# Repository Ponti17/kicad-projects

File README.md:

# KiCad Projects

## Torpedo-III

A clone of ECP audios Torpedo-III amplifier with a few changes:
- Off board PS
- On board output CCS
- Cascade tube CCS
- Constant current heater

## T-GND

A PCB for combining high and low current grounds correctly.

A clone of the PCB from the Wolverine diyAudio thread. Original done by stuartmp

## GND-LIFT

A PCB for lifting circuit ground from chassis ground.

Also a clone of a PCB from the Wolverine diyAudio thread.

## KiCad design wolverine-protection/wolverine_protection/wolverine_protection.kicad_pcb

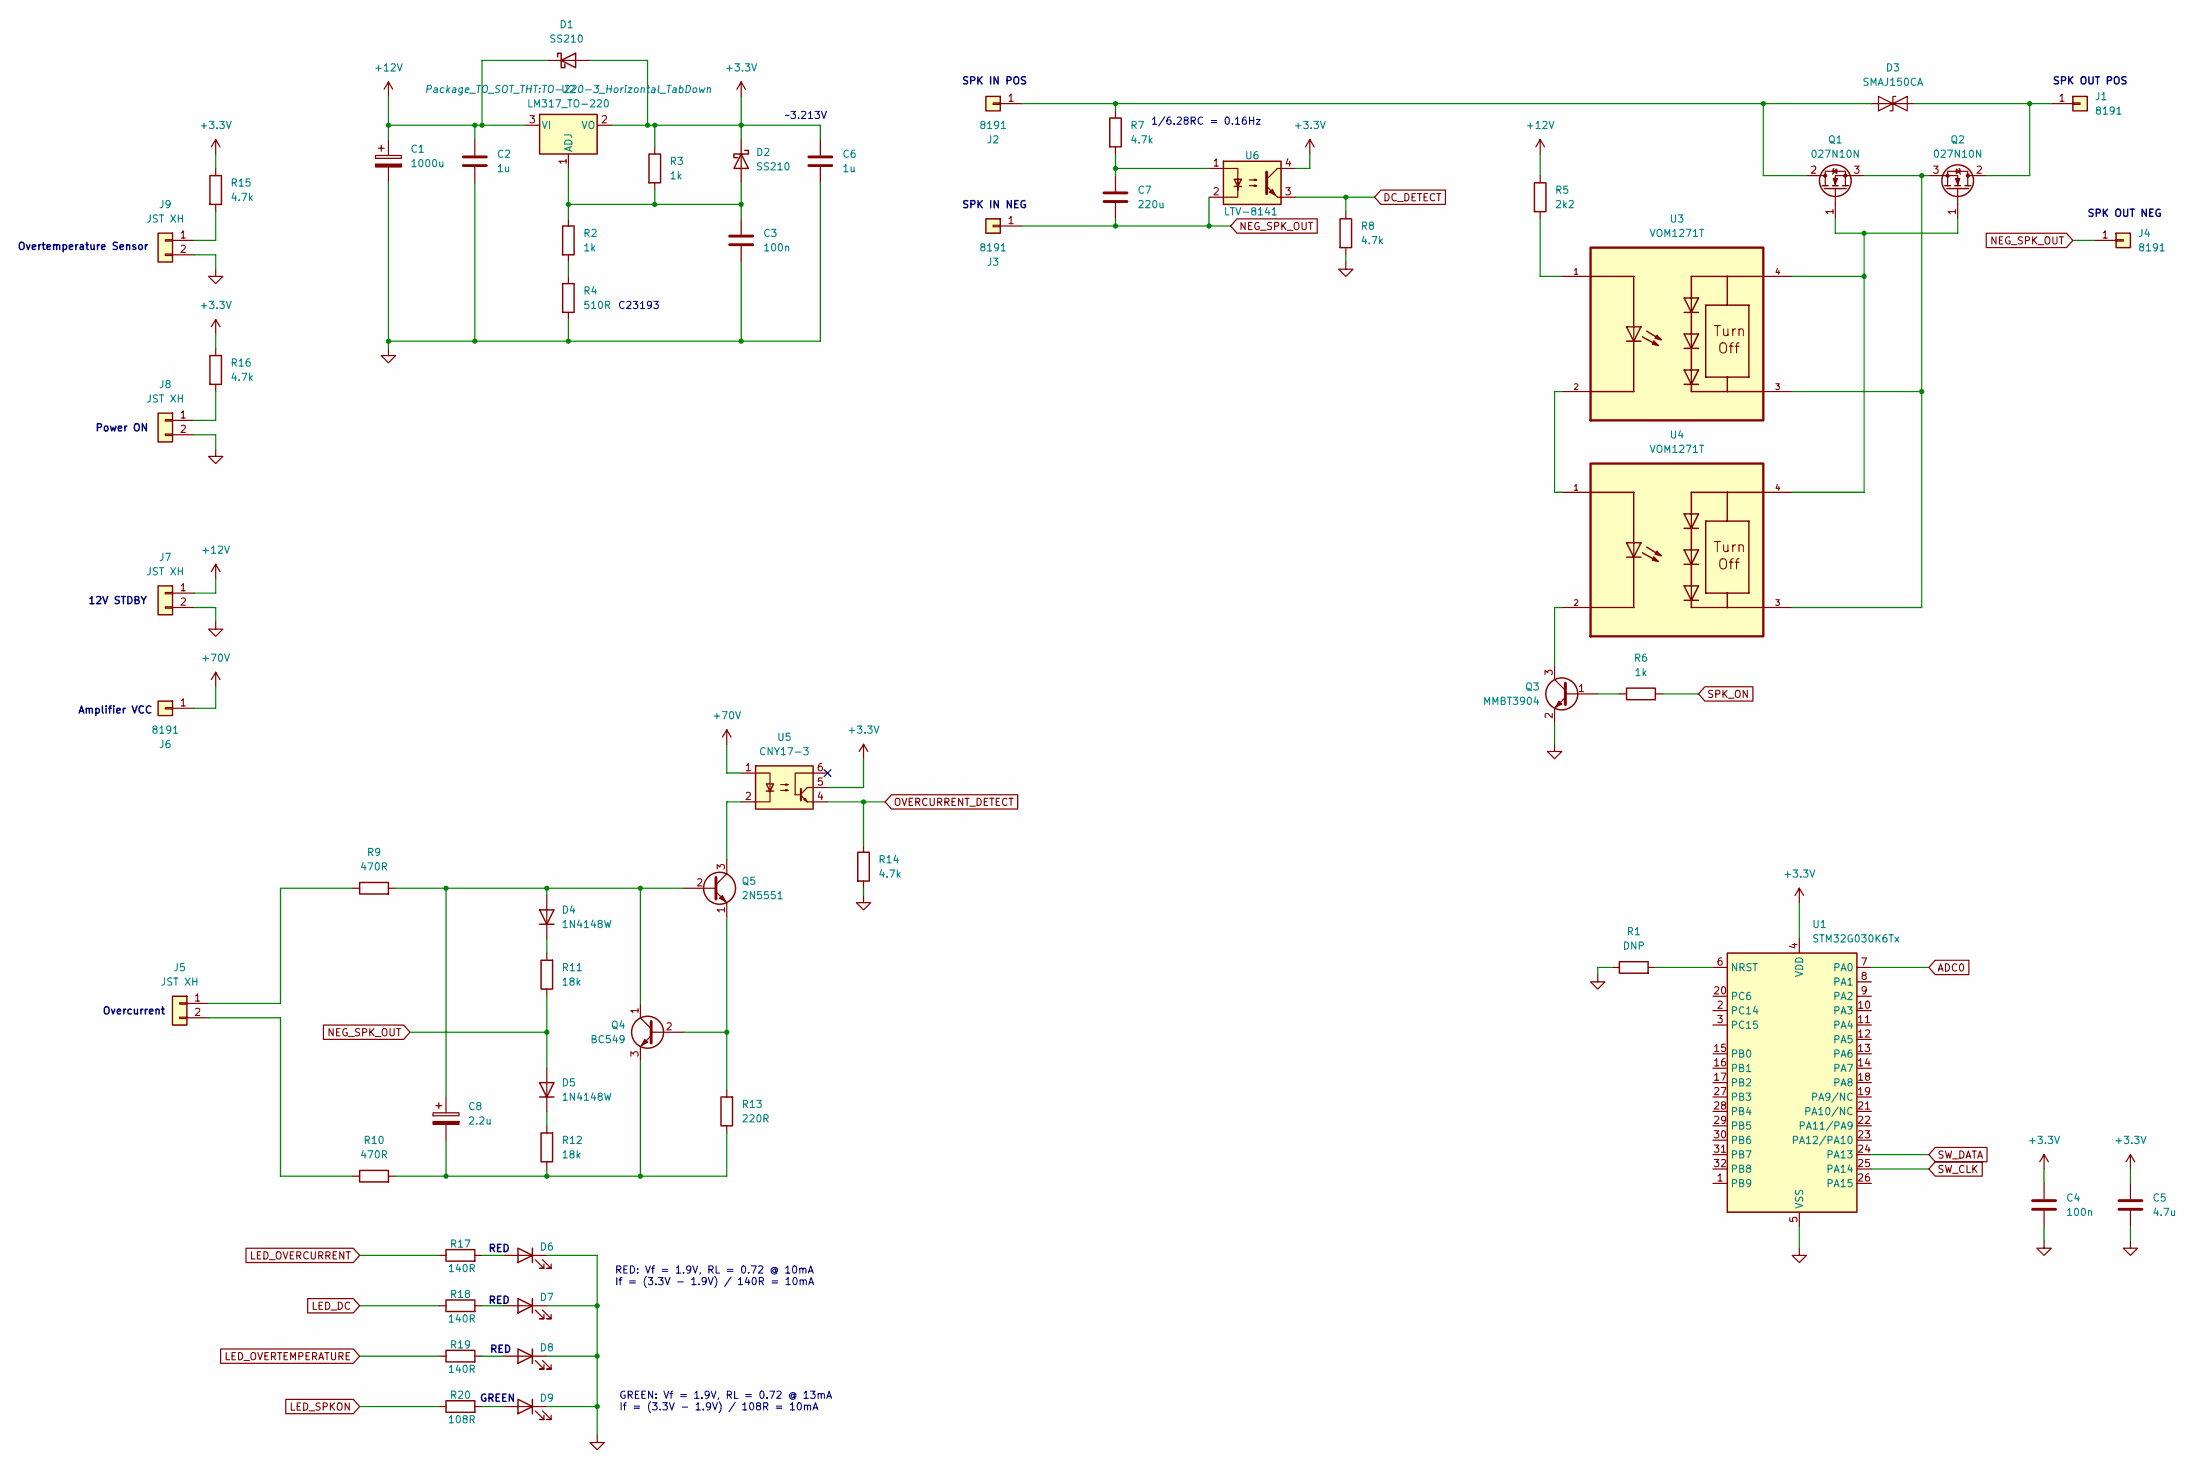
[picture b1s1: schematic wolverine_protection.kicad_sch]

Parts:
C1: 1000u; CP_Radial_D13.0mm_P5.00mm
C2, C6: 1u; C_1206_3216Metric
C3, C4: 100n; C_1206_3216Metric
C5: 4.7u; C_1206_3216Metric
C7: 220u; C_Radial_D12.5mm_H20.0mm_P5.00mm
C8: 2.2u; C_1206_3216Metric
D1, D2: SS210; D_SMA
D3: SMAJ150CA; D_SMA
D4, D5: 1N4148W; D_SOD-123
D6, D7, D8, D9: LED; LED_0805_2012Metric
J1, J2, J3, J4, J6: 8191; KEYSTONE_8191
J5, J7, J8, J9: JST XH; JST_XH_B2B-XH-A_1x02_P2.50mm_Vertical
Q1, Q2: 027N10N; TO-263-2
Q3: MMBT3904; SOT-23
Q4: BC549; TO-92_Inline_Wide
Q5: 2N5551; TO-92_Inline_Wide
R1: DNP; R_1206_3216Metric
R2, R3, R6: 1k; R_1206_3216Metric
R4: 510R; R_1206_3216Metric
R5: 2k2; R_1206_3216Metric
R7, R8, R14, R15, R16: 4.7k; R_1206_3216Metric
R9, R10: 470R; R_1206_3216Metric
R11, R12: 18k; R_1206_3216Metric
R13: 220R; R_1206_3216Metric
R17, R18, R19: 140R; R_1206_3216Metric
R20: 108R; R_1206_3216Metric
U1: STM32G030K6Tx; LQFP-32_7x7mm_P0.8mm
U2: LM317_TO-220; TO-220-3_Horizontal_TabDown
U3, U4: VOM1271T; SOIC254P695X242-4N
U5: CNY17-3; DIP-6_W7.62mm
U6: LTV-8141; DIP-4_W7.62mm

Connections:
+3.3V: C4.1, C5.1, C6.1, D1.2 (A), D2.1 (K), R3.1, R15.1, R16.1, U1.4 (VDD), U2.2 (VO), U5.5, U6.4
+12V: C1.1, C2.1, D1.1 (K), J7.1, R5.1, U2.3 (VI)
+70V: J6.1, U5.1
ADC0: U1.7 (PA0)
DC_DETECT: R8.1, U6.3
GND: C1.2, C2.2, C3.2, C4.2, C5.2, C6.2, D6.1 (K), D7.1 (K), D8.1 (K), D9.1 (K), J7.2, J8.2, J9.2, Q3.2 (E), R1.1, R4.2, R8.2, R14.2, U1.5 (VSS)
LED_DC: R18.1
LED_OVERCURRENT: R17.1
LED_OVERTEMPERATURE: R19.1
LED_SPKON: R20.1
NEG_SPK_OUT: C7.2, D5.2 (A), J3.1, J4.1, R11.1, U6.2
unnamed: C7.1, R7.2, U6.1
unnamed: C3.1, D2.2 (A), R2.1, R3.2, U2.1 (ADJ)
unnamed: D3.1 (A1), J2.1, Q1.2 (D), R7.1
unnamed: D3.2 (A2), J1.1, Q2.2 (D)
unnamed: C8.1, D4.2 (A), Q4.1 (C), Q5.2 (B), R9.2
unnamed: D4.1 (K), R11.2
unnamed: D5.1 (K), R12.2
unnamed: D6.2 (A), R17.2
unnamed: D7.2 (A), R18.2
unnamed: D8.2 (A), R19.2
unnamed: D9.2 (A), R20.2
unnamed: J5.1, R9.1
unnamed: J5.2, R10.1
unnamed: J8.1, R16.2
unnamed: J9.1, R15.2
unnamed: Q1.1 (G), Q2.1 (G), U3.4, U4.4
unnamed: Q1.3 (S), Q2.3 (S), U3.3, U4.3
unnamed: Q3.1 (B), R6.1
unnamed: Q3.3 (C), U4.2
unnamed: Q4.2 (B), Q5.1 (E), R13.2
unnamed: C8.2, Q4.3 (E), R10.2, R12.1, R13.1
unnamed: Q5.3 (C), U5.2
unnamed: R2.2, R4.1
unnamed: R5.2, U3.1
unnamed: R1.2, U1.6 (NRST)
unnamed: U3.2, U4.1
OVERCURRENT_DETECT: R14.1, U5.4
SPK_ON: R6.2
SW_CLK: U1.25 (PA14)
SW_DATA: U1.24 (PA13)

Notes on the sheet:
GREEN
Overtemperature Sensor
Amplifier VCC
RED
~3.213V
C23193
SPK IN POS
1/6.28RC = 0.16Hz
RED: Vf = 1.9V, RL = 0.72 @ 10mA If = (3.3V - 1.9V) / 140R = 10mA
GREEN: Vf = 1.9V, RL = 0.72 @ 13mA If = (3.3V - 1.9V) / 108R = 10mA
Power ON
SPK OUT POS
12V STDBY
SPK OUT NEG
SPK IN NEG
Overcurrent

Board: 2 copper layers, 57 parts (0 on the bottom side), 33 nets, no tracks yet.

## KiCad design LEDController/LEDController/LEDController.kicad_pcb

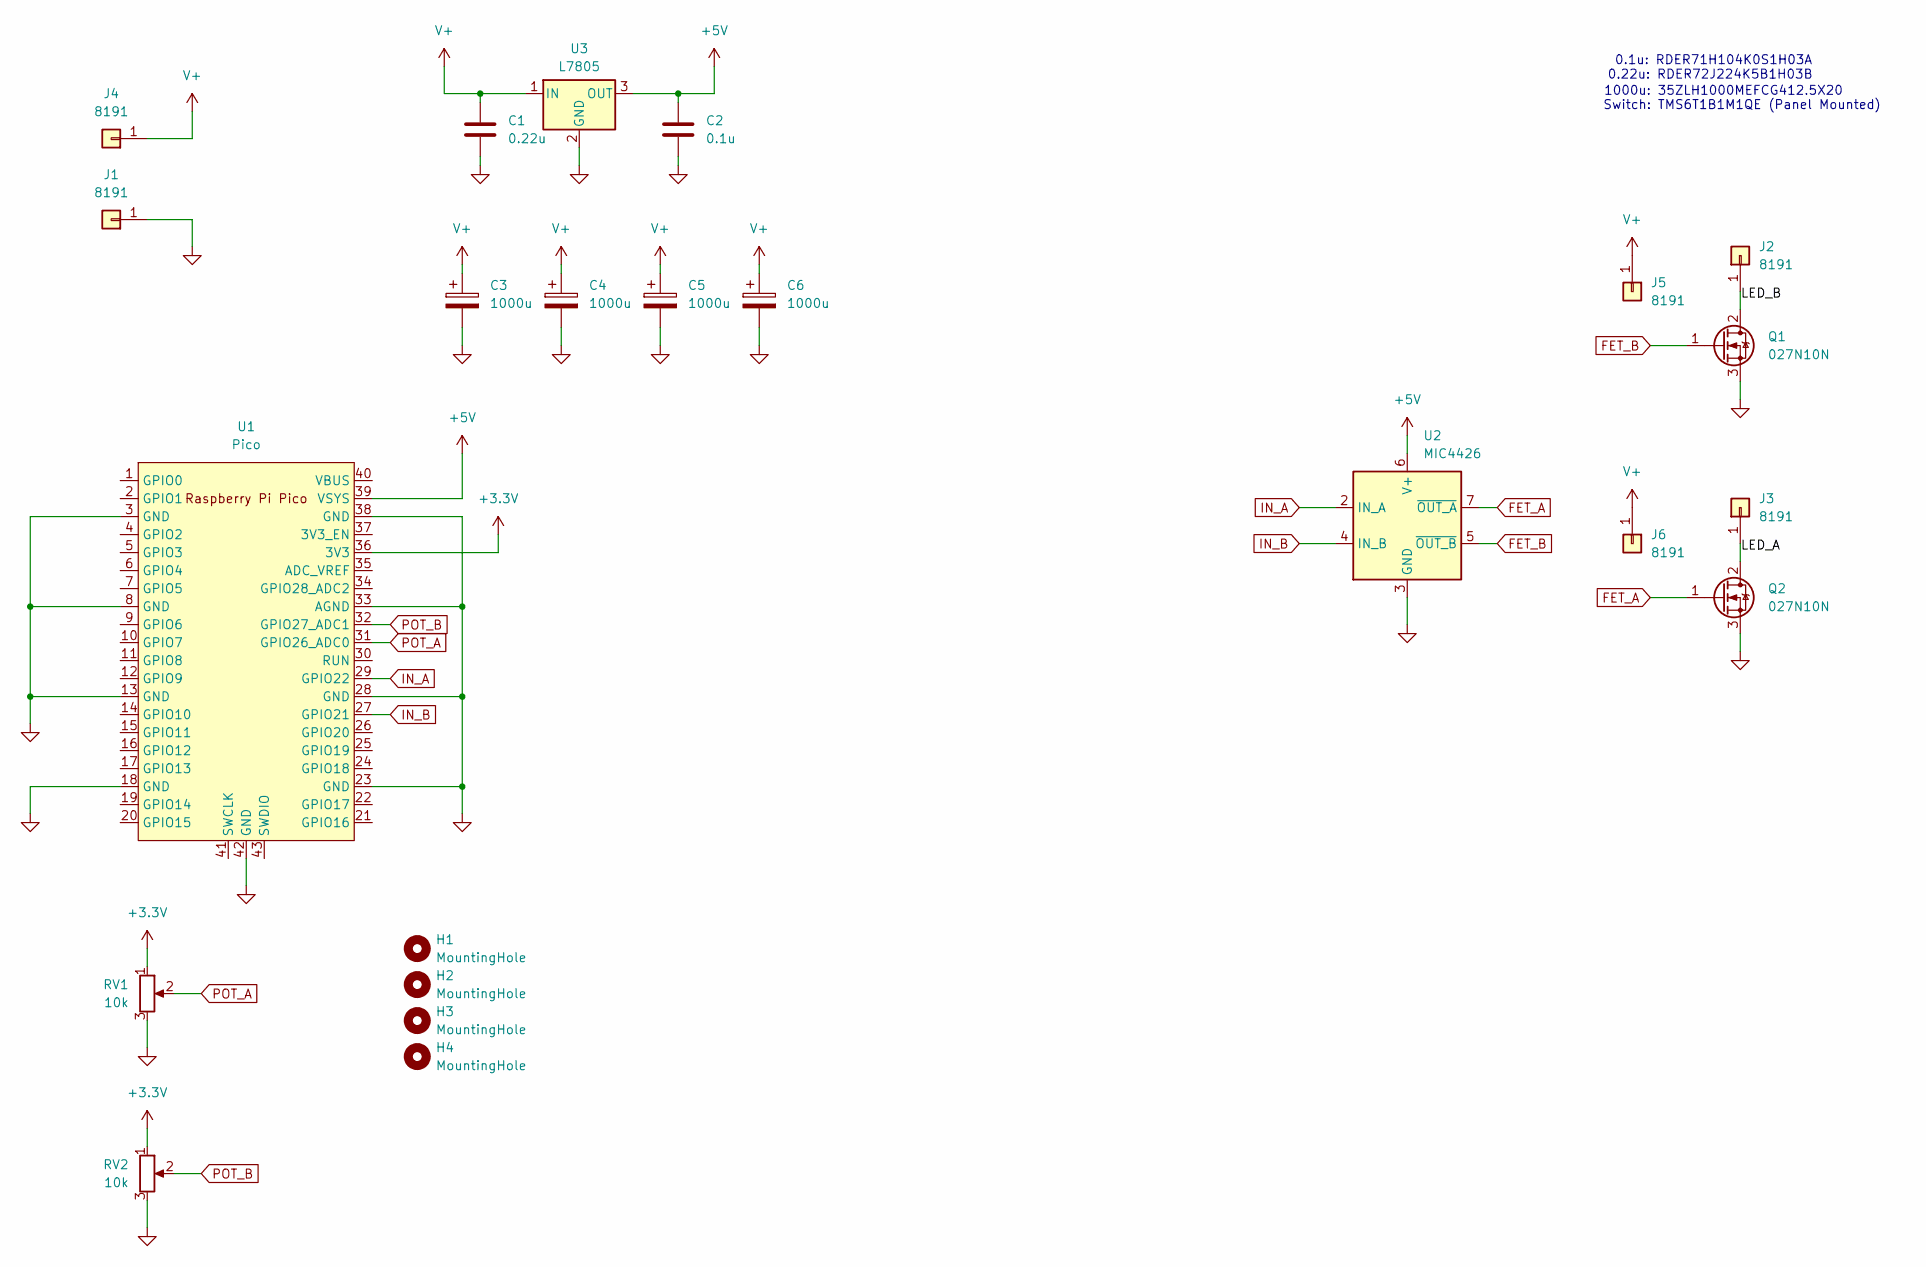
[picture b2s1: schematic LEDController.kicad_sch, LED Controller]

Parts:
C1: 0.22u; C_Disc_D7.5mm_W2.5mm_P5.00mm
C2: 0.1u; C_Disc_D3.8mm_W2.6mm_P2.50mm
C3, C4, C5, C6: 1000u; CP_Radial_D12.5mm_P5.00mm
H1, H2, H3, H4: MountingHole; MountingHole_3.2mm_M3
J1, J2, J3, J4, J5, J6: 8191; KEYSTONE_8191
Q1, Q2: 027N10N; TO-263-2
RV1, RV2: 10k; Potentiometer_Alps_RK09L_Single_Vertical
U1: Pico; RPi_Pico_SMD_TH
U2: MIC4426; DIP-8_W7.62mm
U3: L7805; TO-220-3_Horizontal_TabDown

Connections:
+3.3V: RV1.1, RV2.1, U1.36 (3V3)
+5V: C2.1, U1.39 (VSYS), U2.6 (V+), U3.3 (OUT)
/LED_A: J3.1, Q2.2 (D)
/LED_B: J2.1, Q1.2 (D)
FET_A: Q2.1 (G), U2.7 (~OUT_A)
FET_B: Q1.1 (G), U2.5 (~OUT_B)
GND: C1.2, C2.2, C3.2, C4.2, C5.2, C6.2, J1.1, Q1.3 (S), Q2.3 (S), RV1.3, RV2.3, U1.3 (GND), U1.8 (GND), U1.13 (GND), U1.18 (GND), U1.23 (GND), U1.28 (GND), U1.33 (AGND), U1.38 (GND), U1.42 (GND), U2.3 (GND), U3.2 (GND)
IN_A: U1.29 (GPIO22), U2.2 (IN_A)
IN_B: U1.27 (GPIO21), U2.4 (IN_B)
POT_A: RV1.2, U1.31 (GPIO26_ADC0)
POT_B: RV2.2, U1.32 (GPIO27_ADC1)
V+: C1.1, C3.1, C4.1, C5.1, C6.1, J4.1, J5.1, J6.1, U3.1 (IN)

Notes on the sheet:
0.22u: RDER72J224K5B1H03B
Switch: TMS6T1B1M1QE (Panel Mounted)
1000u: 35ZLH1000MEFCG412.5X20
0.1u: RDER71H104K0S1H03A

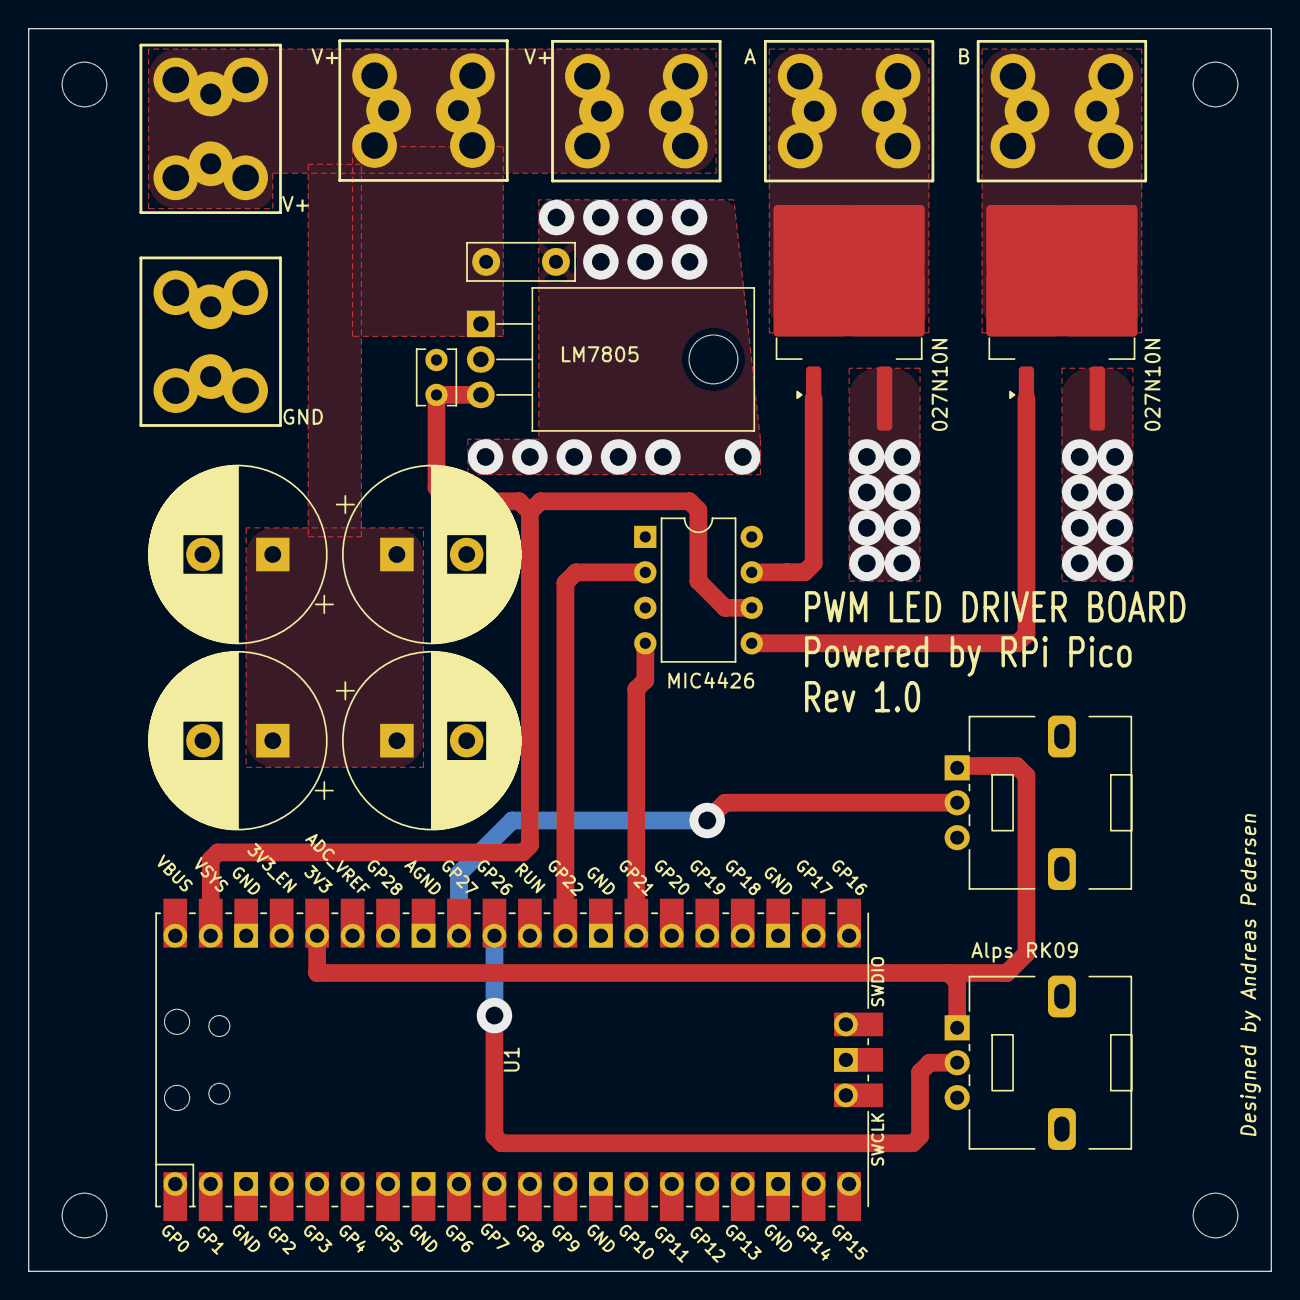
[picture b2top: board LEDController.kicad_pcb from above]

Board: 2 copper layers, 89.0 x 89.0 mm, 23 parts (0 on the bottom side), 12 nets.

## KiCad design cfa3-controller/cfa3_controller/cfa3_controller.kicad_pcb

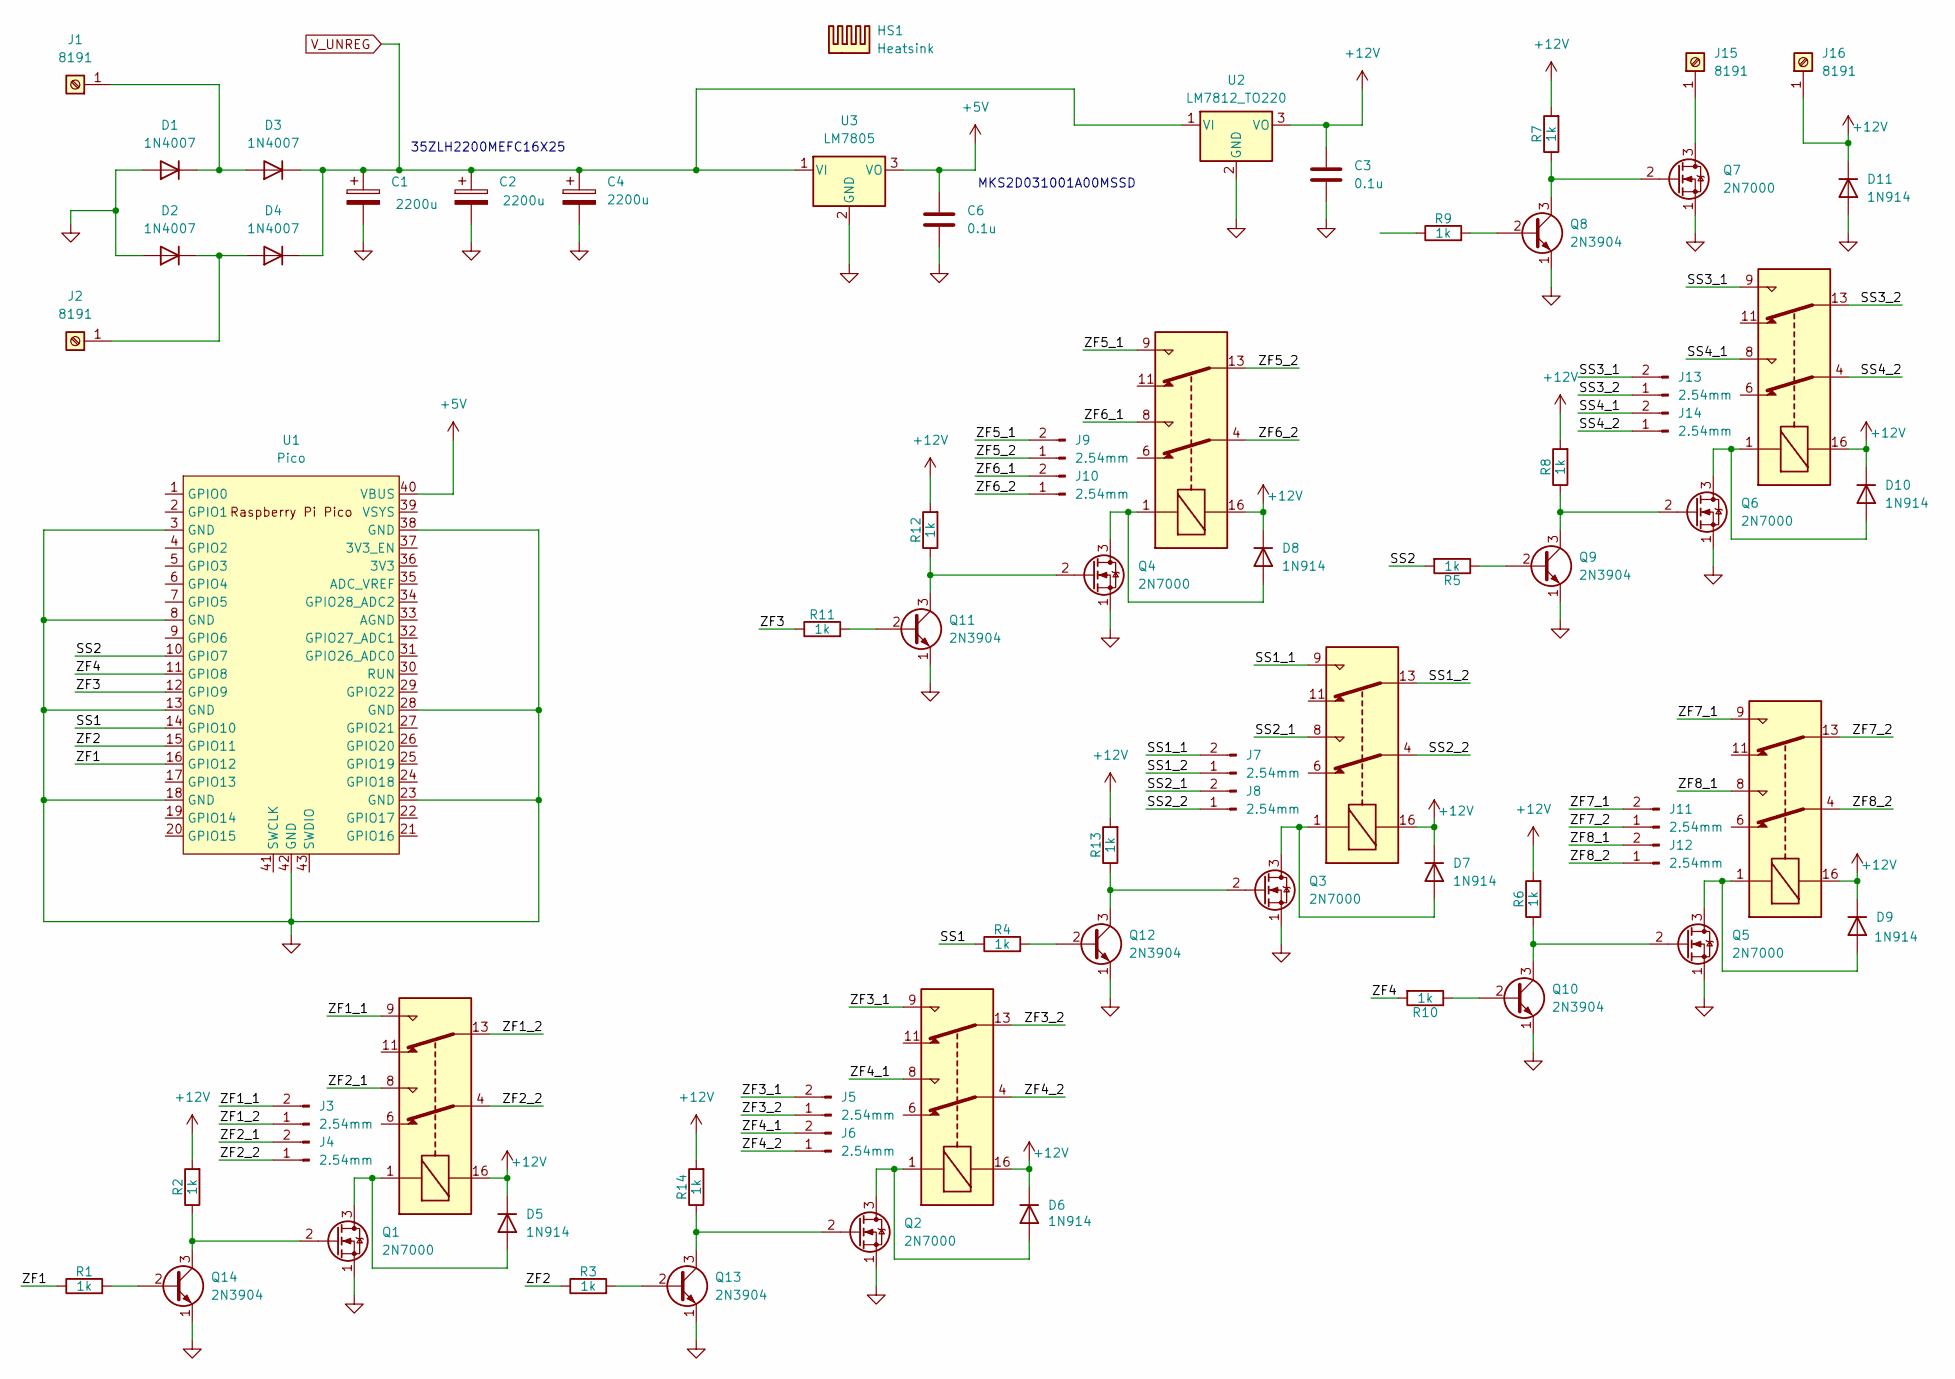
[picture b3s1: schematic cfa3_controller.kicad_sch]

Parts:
C1, C2, C4: 2200u; CP_Radial_D16.0mm_P7.50mm
C3, C6: 0.1u; C_Rect_L7.0mm_W2.5mm_P5.00mm
D1, D2, D3, D4: 1N4007; D_DO-41_SOD81_P10.16mm_Horizontal
D5, D6, D7, D8, D9, D10, D11: 1N914; D_DO-35_SOD27_P7.62mm_Horizontal
HS1: Heatsink; Heatsink_Fischer_SK104-STCB_35x13mm__2xDrill3.5mm_ScrewM3
J1, J2, J15, J16: 8191; KEYSTONE_8191
J3, J4, J5, J6, J7, J8, J9, J10, J11, J12, J13, J14: 2.54mm; PinHeader_1x02_P2.54mm_Vertical
K1, K2, K3, K4, K5, K6: G5V-2; Relay_DPDT_Omron_G5V-2
Q1, Q2, Q3, Q4, Q5, Q6, Q7: 2N7000; TO-92_Inline_Wide
Q8, Q9, Q10, Q11, Q12, Q13, Q14: 2N3904; TO-92L_Inline_Wide
R1, R2, R3, R4, R5, R6, R7, R8, R9, R10, R11, R12, R13, R14: 1k; R_Axial_DIN0207_L6.3mm_D2.5mm_P5.08mm_Vertical
U1: Pico; RPi_Pico_SMD_TH
U2: LM7812_TO220; TO-220-3_Vertical
U3: LM7805; TO-220-3_Vertical

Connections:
+5V: C6.1, U1.40 (VBUS), U3.3 (VO)
+12V: C3.1, D5.1 (K), D6.1 (K), D7.1 (K), D8.1 (K), D9.1 (K), D10.1 (K), D11.1 (K), J16.1, K1.16, K2.16, K3.16, K4.16, K5.16, K6.16, R2.2, R6.2, R7.2, R8.2, R12.2, R13.2, R14.2, U2.3 (VO)
/SS1: R4.1, U1.14 (GPIO10)
/SS1_1: J7.2, K3.9
/SS1_2: J7.1, K3.13
/SS2: R5.2, U1.10 (GPIO7)
/SS2_1: J8.2, K3.8
/SS2_2: J8.1, K3.4
/SS3_1: J13.2, K6.9
/SS3_2: J13.1, K6.13
/SS4_1: J14.2, K6.8
/SS4_2: J14.1, K6.4
/ZF1: R1.1, U1.16 (GPIO12)
/ZF1_1: J3.2, K1.9
/ZF1_2: J3.1, K1.13
/ZF2: R3.1, U1.15 (GPIO11)
/ZF2_1: J4.2, K1.8
/ZF2_2: J4.1, K1.4
/ZF3: R11.1, U1.12 (GPIO9)
/ZF3_1: J5.2, K2.9
/ZF3_2: J5.1, K2.13
/ZF4: R10.2, U1.11 (GPIO8)
/ZF4_1: J6.2, K2.8
/ZF4_2: J6.1, K2.4
/ZF5_1: J9.2, K4.9
/ZF5_2: J9.1, K4.13
/ZF6_1: J10.2, K4.8
/ZF6_2: J10.1, K4.4
/ZF7_1: J11.2, K5.9
/ZF7_2: J11.1, K5.13
/ZF8_1: J12.2, K5.8
/ZF8_2: J12.1, K5.4
GND: C1.2, C2.2, C3.2, C4.2, C6.2, D1.2 (A), D2.2 (A), D11.2 (A), Q1.1 (S), Q2.1 (S), Q3.1 (S), Q4.1 (S), Q5.1 (S), Q6.1 (S), Q7.1 (S), Q8.1 (E), Q9.1 (E), Q10.1 (E), Q11.1 (E), Q12.1 (E), Q13.1 (E), Q14.1 (E), U1.3 (GND), U1.8 (GND), U1.13 (GND), U1.18 (GND), U1.23 (GND), U1.28 (GND), U1.38 (GND), U1.42 (GND), U2.2 (GND), U3.2 (GND)
unnamed: D1.1 (K), D3.2 (A), J1.1
unnamed: D2.1 (K), D4.2 (A), J2.1
unnamed: D5.2 (A), K1.1, Q1.3 (D)
unnamed: D6.2 (A), K2.1, Q2.3 (D)
unnamed: D7.2 (A), K3.1, Q3.3 (D)
unnamed: D8.2 (A), K4.1, Q4.3 (D)
unnamed: D9.2 (A), K5.1, Q5.3 (D)
unnamed: D10.2 (A), K6.1, Q6.3 (D)
unnamed: J15.1, Q7.3 (D)
unnamed: Q1.2 (G), Q14.3 (C), R2.1
unnamed: Q6.2 (G), Q9.3 (C), R8.1
unnamed: Q7.2 (G), Q8.3 (C), R7.1
unnamed: Q8.2 (B), R9.2
unnamed: Q9.2 (B), R5.1
unnamed: Q10.2 (B), R10.1
unnamed: Q5.2 (G), Q10.3 (C), R6.1
unnamed: Q11.2 (B), R11.2
unnamed: Q4.2 (G), Q11.3 (C), R12.1
unnamed: Q12.2 (B), R4.2
unnamed: Q3.2 (G), Q12.3 (C), R13.1
unnamed: Q13.2 (B), R3.2
unnamed: Q2.2 (G), Q13.3 (C), R14.1
unnamed: Q14.2 (B), R1.2
V_UNREG: C1.1, C2.1, C4.1, D3.1 (K), D4.1 (K), U2.1 (VI), U3.1 (VI)

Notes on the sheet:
35ZLH2200MEFC16X25
MKS2D031001A00MSSD

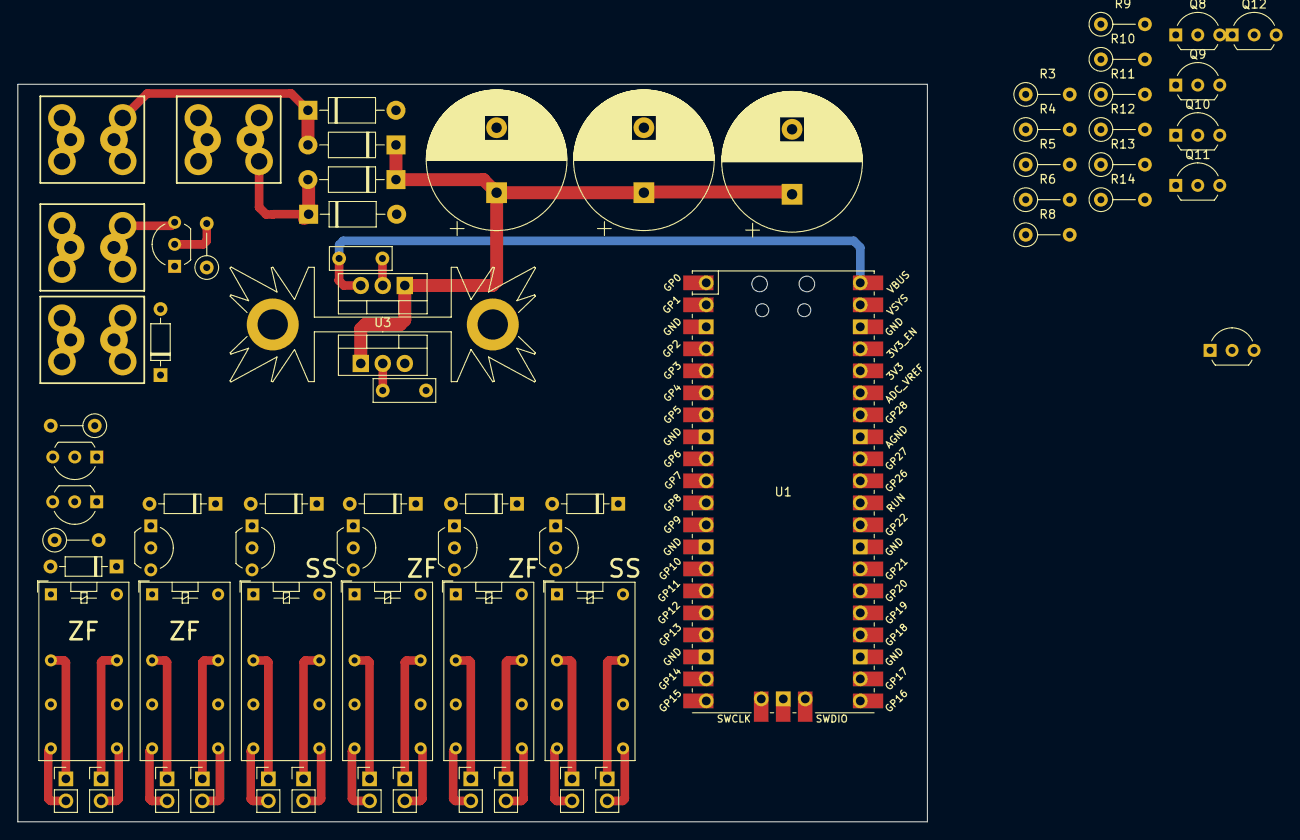
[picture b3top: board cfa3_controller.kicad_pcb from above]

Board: 2 copper layers, 105.0 x 85.1 mm, 70 parts (0 on the bottom side), 57 nets.

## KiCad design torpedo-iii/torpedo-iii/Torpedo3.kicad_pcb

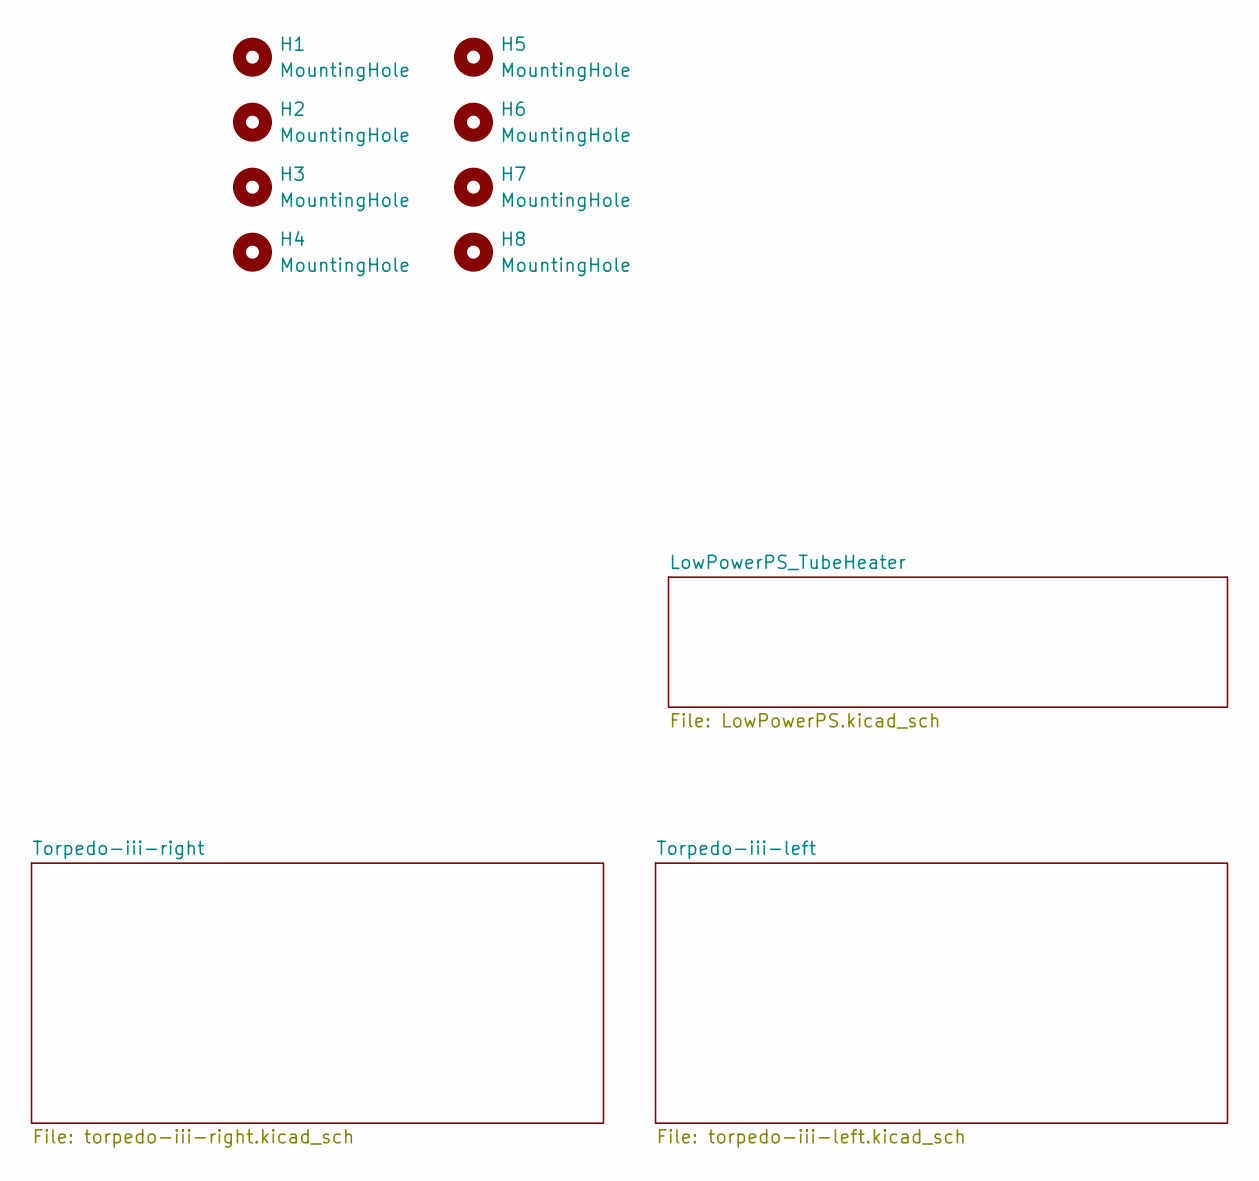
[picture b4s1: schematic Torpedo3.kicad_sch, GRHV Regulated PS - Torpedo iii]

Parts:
H1, H2, H3, H4, H5, H6, H7, H8: MountingHole; MountingHole_3.5mm

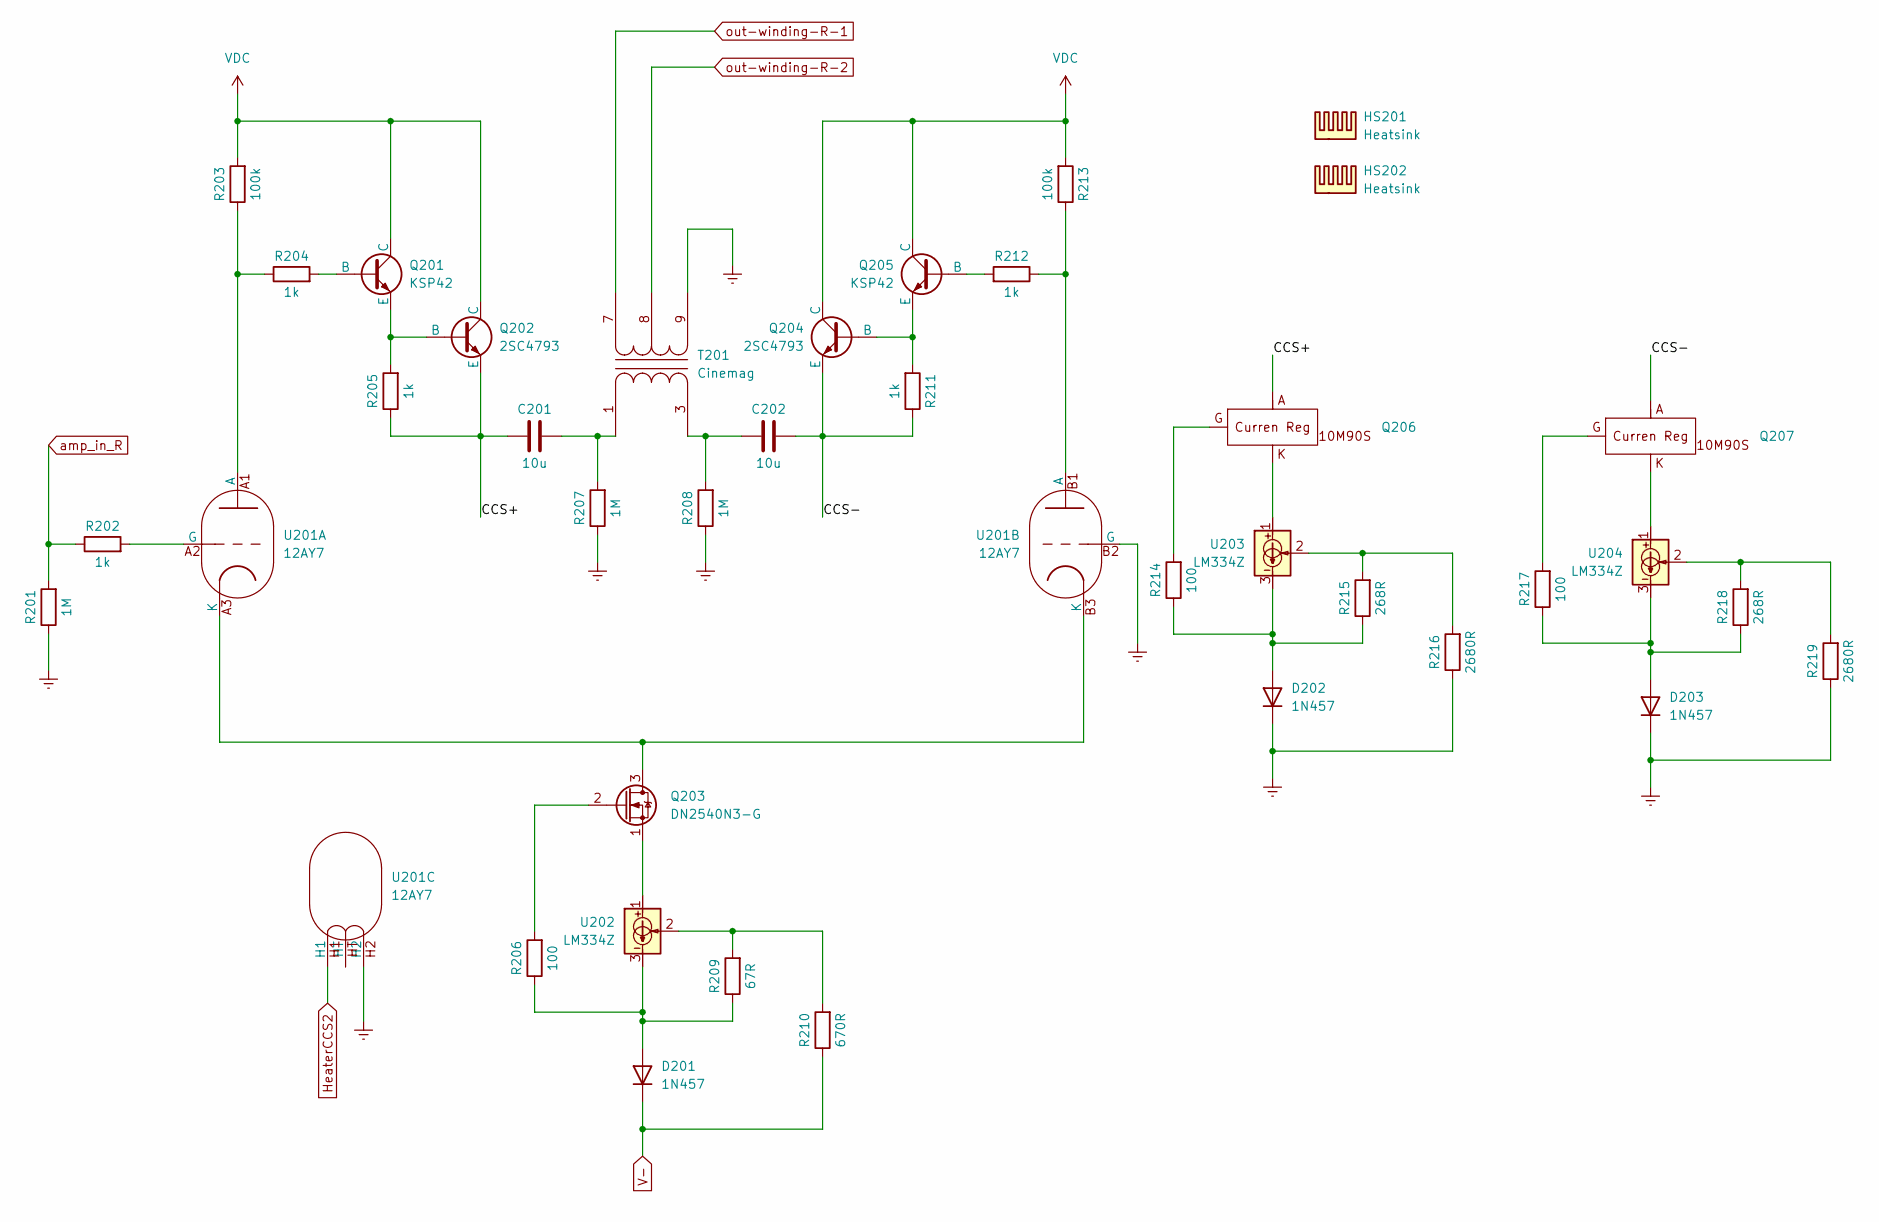
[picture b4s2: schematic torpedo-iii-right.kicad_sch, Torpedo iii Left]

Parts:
C201, C202: 10u; Mundorf Evo 10u
D201, D202, D203: 1N457; D_DO-35_SOD27_P7.62mm_Horizontal
HS201, HS202: Heatsink; 513102B02500G
Q201, Q205: KSP42; TO-92_Inline_Wide
Q202, Q204: 2SC4793; TO-220-3_Vertical
Q203: DN2540N3-G; TO-92_Inline_Wide
Q206, Q207: TO-220-3_Vertical
R201, R207, R208: 1M; R_Axial_DIN0309_L9.0mm_D3.2mm_P12.70mm_Horizontal
R202, R204, R205, R211, R212: 1k; R_Axial_DIN0309_L9.0mm_D3.2mm_P12.70mm_Horizontal
R203, R213: 100k; R_Axial_DIN0414_L11.9mm_D4.5mm_P15.24mm_Horizontal
R206, R214, R217: 100; R_Axial_DIN0309_L9.0mm_D3.2mm_P12.70mm_Horizontal
R209: 67R; R_Axial_DIN0309_L9.0mm_D3.2mm_P12.70mm_Horizontal
R210: 670R; R_Axial_DIN0309_L9.0mm_D3.2mm_P12.70mm_Horizontal
R215, R218: 268R; R_Axial_DIN0309_L9.0mm_D3.2mm_P12.70mm_Horizontal
R216, R219: 2680R; R_Axial_DIN0309_L9.0mm_D3.2mm_P12.70mm_Horizontal
T201: Cinemag; Cinemag CM-15615PC
U201: 12AY7
U202, U203, U204: LM334Z; TO-92_Inline_Wide

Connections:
/Torpedo-iii-right/CCS+: C201.1, Q202.3 (E), Q206.2, R205.1
/Torpedo-iii-right/CCS-: C202.1, Q204.3 (E), Q207.2, R211.1
GNDREF: D202.1 (K), D203.1 (K), R201.1, R207.1, R208.1, R216.1, R219.1, T201.9 (SA), U201.B2 (G), U201.H2; also elsewhere on the board
HeaterCCS2: U201.H1; also elsewhere on the board
unnamed: D201.2 (A), R206.1, R209.1, U202.3
unnamed: D202.2 (A), R214.1, R215.1, U203.3
unnamed: D203.2 (A), R217.1, R218.1, U204.3
unnamed: Q201.2 (B), R204.2
unnamed: Q201.1 (E), Q202.1 (B), R205.2
unnamed: Q203.3 (D), U201.A3 (K), U201.B3 (K)
unnamed: Q203.2 (G), R206.2
unnamed: Q203.1 (S), U202.1
unnamed: Q204.1 (B), Q205.1 (E), R211.2
unnamed: Q205.2 (B), R212.2
unnamed: Q206.1, R214.2
unnamed: Q206.3, U203.1
unnamed: Q207.1, R217.2
unnamed: Q207.3, U204.1
unnamed: R209.2, R210.2, U202.2
unnamed: R215.2, R216.2, U203.2
unnamed: R218.2, R219.2, U204.2
unnamed: C201.2, R207.2, T201.1 (AA)
unnamed: C202.2, R208.2, T201.3 (AB)
unnamed: R203.1, R204.1, U201.A1 (A)
unnamed: R202.2, U201.A2 (G)
unnamed: R212.1, R213.1, U201.B1 (A)
V-: D201.1 (K), R210.1; also elsewhere on the board
VDC: Q201.3 (C), Q202.2 (C), Q204.2 (C), Q205.3 (C), R203.2, R213.2; also elsewhere on the board
amp_in_R: R201.2, R202.1; also elsewhere on the board
out-winding-R-1: T201.7 (SB); also elsewhere on the board
out-winding-R-2: T201.8 (SC); also elsewhere on the board
